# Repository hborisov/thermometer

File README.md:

# thermometer

https://hristoborisov.wordpress.com/digital-thermometer-with-pic-mcu-and-tmp102-sensor/

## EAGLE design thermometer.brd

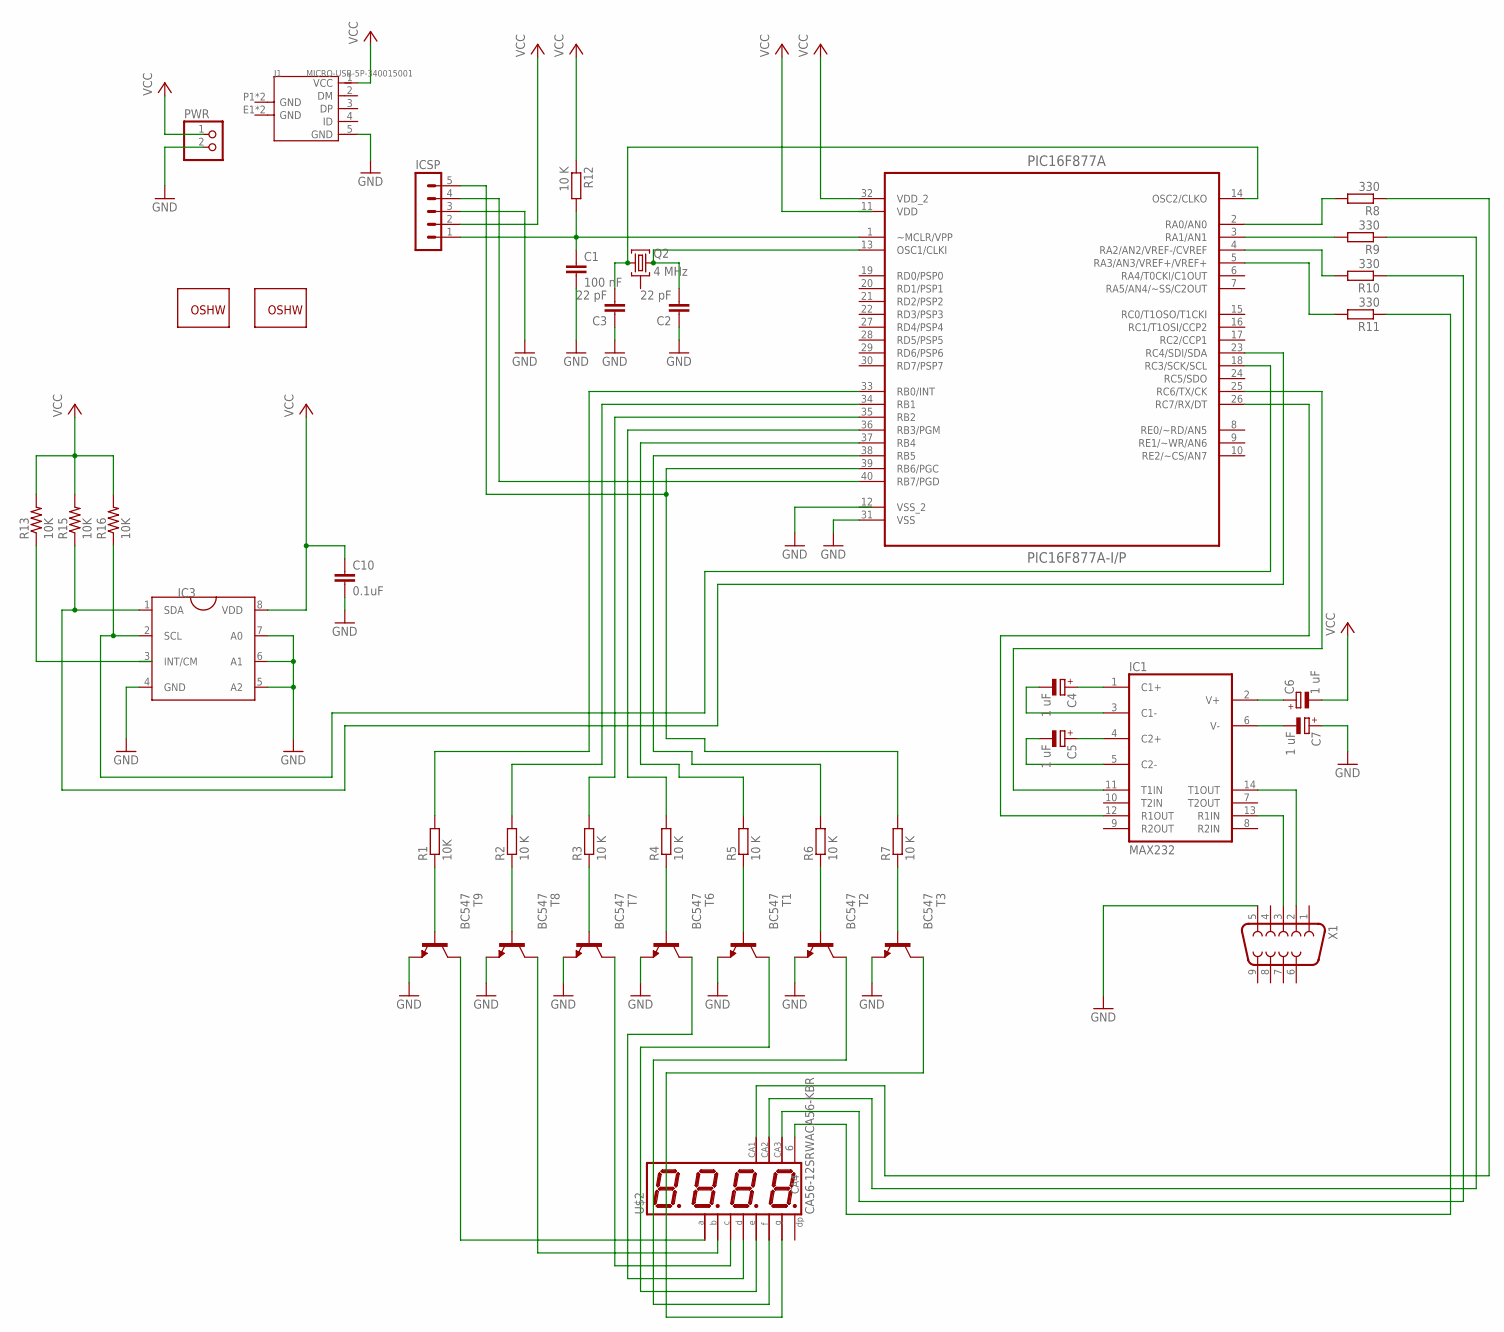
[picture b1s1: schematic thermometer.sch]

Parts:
C1: 100 nF; C050-025X075
C2, C3: 22 pF; C050-025X075
C4, C5, C6, C7: 1 uF; E1,8-4
C10: 0.1uF; 0603-CAP
GOLD_ORB_SM1: OSHWLOGO_GOLD_ORB_LG; OSHW0
GOLD_ORB_SM2: OSHWLOGO_GOLD_ORB_SM; OSHW2
IC1: MAX232; DIL16
IC3: TCN75TCN75MUA; MSOP8
ICSP: MA05-1
J1: MICRO-USB-5P-340015001; B-SMD-5P
PIC16F877A: PIC16F877A-I/P; DIP254P1524X483-40
PWR: PINHD-1X2; 1X02
Q2: 4 MHz; UM1
R1: 10K; 0207/10
R2, R3, R4, R5, R6, R7: 10 K; 0207/10
R8, R9, R10, R11: 330; 0204/7
R12: 10 K; 0204/7
R13, R15, R16: 10K; 0603-RES
T1, T2, T3, T6, T7, T8, T9: BC547; TO92
U$2: CA56-12SRWACA56-KBR; CA56
X1: F09HP

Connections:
GND: C1.2, C2.1, C3.1, C7.+, C10.2, IC1.15 (GND), IC3.4 (GND), IC3.5 (A2), IC3.6 (A1), IC3.7 (A0), ICSP.3, J1.5 (GND), PIC16F877A.31 (VSS), PWR.2, T1.1 (E), T2.1 (E), T3.1 (E), T6.1 (E), T7.1 (E), T8.1 (E), T9.1 (E), X1.5
unnamed: R1.1, T9.2 (B)
unnamed: R2.1, T8.2 (B)
unnamed: R3.1, T7.2 (B)
unnamed: R4.1, T6.2 (B)
unnamed: R5.1, T1.2 (B)
unnamed: R6.1, T2.2 (B)
unnamed: R7.1, T3.2 (B)
unnamed: PIC16F877A.33 (RB0/INT), R1.2
unnamed: PIC16F877A.34 (RB1), R2.2
unnamed: PIC16F877A.35 (RB2), R3.2
unnamed: PIC16F877A.36 (RB3/PGM), R4.2
unnamed: PIC16F877A.37 (RB4), R5.2
unnamed: PIC16F877A.38 (RB5), R6.2
unnamed: ICSP.5, PIC16F877A.39 (RB6/PGC), R7.2
unnamed: PIC16F877A.2 (RA0/AN0), R8.2
unnamed: PIC16F877A.3 (RA1/AN1), R9.2
unnamed: PIC16F877A.4 (RA2/AN2/VREF-/CVREF), R10.2
unnamed: PIC16F877A.5 (RA3/AN3/VREF+/VREF+), R11.2
unnamed: R8.1, U$2.12 (CA)
unnamed: C1.1, ICSP.1, PIC16F877A.1 (~MCLR/VPP), R12.2
unnamed: R9.1, U$2.9 (CA)
unnamed: R10.1, U$2.8 (CA)
unnamed: T9.3 (C), U$2.11 (A)
unnamed: C2.2, PIC16F877A.13 (OSC1/CLKI), Q2.3
unnamed: T7.3 (C), U$2.4 (C)
unnamed: T6.3 (C), U$2.2 (D)
unnamed: T1.3 (C), U$2.1 (E)
unnamed: T2.3 (C), U$2.10 (F)
unnamed: T3.3 (C), U$2.5 (G)
unnamed: ICSP.4, PIC16F877A.40 (RB7/PGD)
unnamed: R11.1, U$2.6 (CA4)
unnamed: IC3.2 (SCL), PIC16F877A.18 (RC3/SCK/SCL), R16.1
unnamed: IC3.1 (SDA), PIC16F877A.23 (RC4/SDI/SDA), R15.1
unnamed: C7.-, IC1.6 (V-)
unnamed: C3.2, PIC16F877A.14 (OSC2/CLKO), Q2.1
unnamed: C6.+, IC1.2 (V+)
unnamed: C4.+, IC1.1 (C1+)
unnamed: C4.-, IC1.3 (C1-)
unnamed: C5.+, IC1.4 (C2+)
unnamed: C5.-, IC1.5 (C2-)
unnamed: IC1.11 (T1IN), PIC16F877A.25 (RC6/TX/CK)
unnamed: IC1.14 (T1OUT), X1.2
unnamed: IC1.13 (R1IN), X1.3
unnamed: IC1.12 (R1OUT), PIC16F877A.26 (RC7/RX/DT)
unnamed: T8.3 (C), U$2.7 (B)
unnamed: IC3.3 (INT/CM), R13.1
VCC: C6.-, C10.1, IC1.16 (VCC), IC3.8 (VDD), ICSP.2, J1.1 (VCC), PIC16F877A.32 (VDD_2), PWR.1, R12.1, R13.2, R15.2, R16.2
VDD: PIC16F877A.11 (VDD)
VSS_2: PIC16F877A.12 (VSS_2)

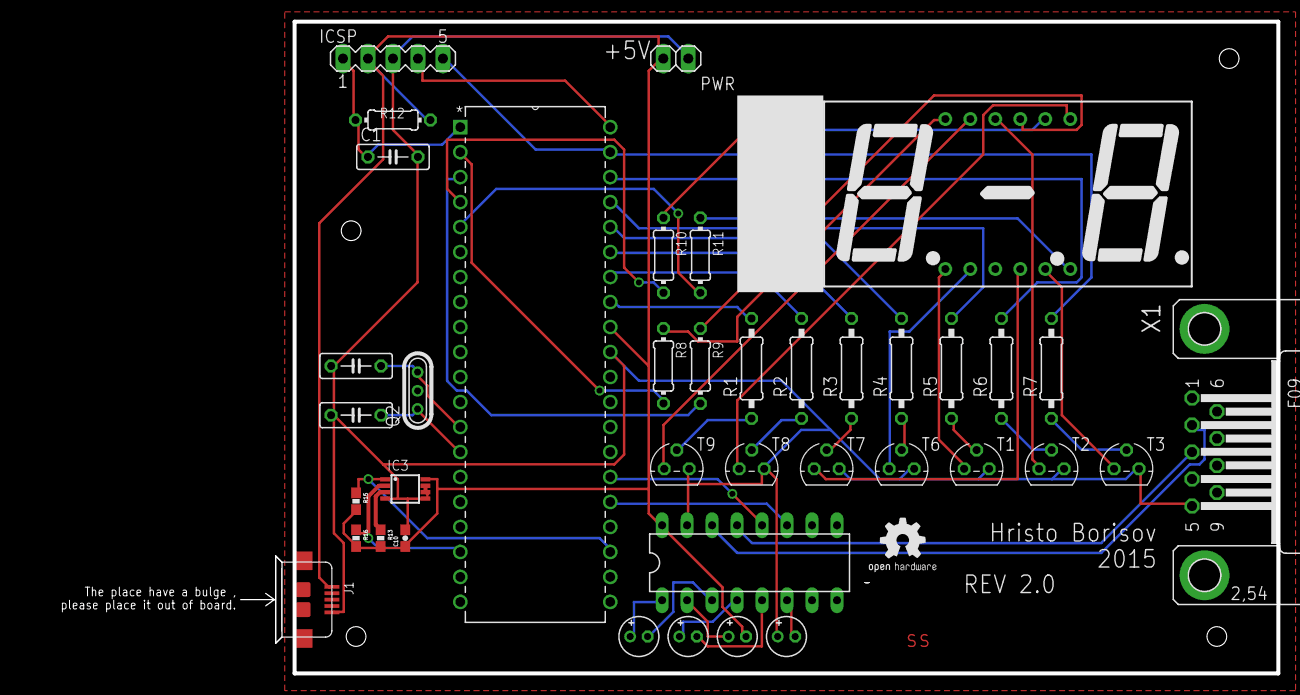
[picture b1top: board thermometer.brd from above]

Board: 2 copper layers, 127.7 x 66.2 mm, 41 parts (1 on the bottom side), 48 nets.

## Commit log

2014-06-16 indication shows 1234
2014-06-16 swap routine implemented
2014-06-16 un track build and dist folders
2014-06-17 starting with floating points
2014-06-17 I cann convert integers to float and multiply floats. Coooooooool
2014-06-21 Thermometer ready. Wait routine fixed! It turns out that pagesel have to be used since the program is larger that a single page of 2K.
2014-06-22 The program works with interrupts but there is a problem if wait is called inside the interrupt service routine. Keep investigating...
2014-06-22 First version ready!
2014-06-22 First version bug fixed :)
2014-09-13 sensor sends data to gateway! The bug with the redundant txpolls is fixed. You have to reset the MSSP port in the beginning of each interrupt!
2014-09-13 sensor pushes to gateway
2014-09-14 Command interface added. System works end to end :)
2014-09-21 intermediate
2015-02-18 Thermometer circuit and board v1.0
2015-02-21 Final version
2015-02-21 v 1.1 released. Several bug fixes
2015-02-21 Adding schematic and board as images
2015-02-23 Version 2.0 with TCN75 and USB Micro B
2015-02-23 Adding schematic and board pictures
2015-02-23 Changing schematic pictures
2015-02-23 Adding some text and Open Hardware logo
2015-06-23 adding the source code for the thermometer
2015-06-23 rename of the project
2015-06-23 adding again the thermometer project
2015-06-23 tcn75 section
2015-06-23 tmp102 version
2015-06-23 again tcn75 version
2015-06-25 added workaround for faulty reading on tcn75
2015-10-23 Adding box rev 1 3d model.

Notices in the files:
parts and their libraries:
SparkFun-Resistors: Licensing: Creative Commons ShareAlike 4.0 International - https://creativecommons.org/licenses/by-sa/4.0
